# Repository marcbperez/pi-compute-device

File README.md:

# pi-compute-device

A portable device built with the Raspberry Pi Compute module.

## Installation

The schematics project is done in KiCad, free and available to most common
platforms. More information on how to download and install KiCad can be found in
its [official download page][download-kicad].

## Usage

Clone the sources and browse the package folder. The KiCad project is located in
`kicad-project/pi-compute-device.pro`.

```bash
git clone https://github.com/marcbperez/pi-compute-device
cd pi-compute-device
```

## Testing

There is no testing in place for this project yet.

## Troubleshooting

The [issue tracker][issue-tracker] intends to manage and compile bugs,
enhancements, proposals and tasks. Reading through its material or reporting to
its contributors via the platform is strongly recommended.

## Contributing

This project adheres to [Semantic Versioning][semver] and to certain syntax
conventions defined in [.editorconfig][editorconfig]. To get a list of changes
refer to the [CHANGELOG][changelog]. Only branches prefixed by *feature-*,
*hotfix-*, or *release-* will be considered:

  - Fork the project.
  - Create your new branch: `git checkout -b feature-my-feature develop`
  - Commit your changes: `git commit -am 'Added my new feature.'`
  - Push the branch: `git push origin feature-my-feature`
  - Submit a pull request.

## Credits

This project is created by [marcbperez][author] and maintained by its
[author][author] and contributors.

## License

This project is licensed under the [Apache License Version 2.0][license].

[author]: https://marcbperez.github.io
[issue-tracker]: https://github.com/marcbperez/pi-compute-device/issues
[editorconfig]: .editorconfig
[changelog]: CHANGELOG.md
[license]: LICENSE
[semver]: http://semver.org
[download-kicad]: http://kicad-pcb.org/download/

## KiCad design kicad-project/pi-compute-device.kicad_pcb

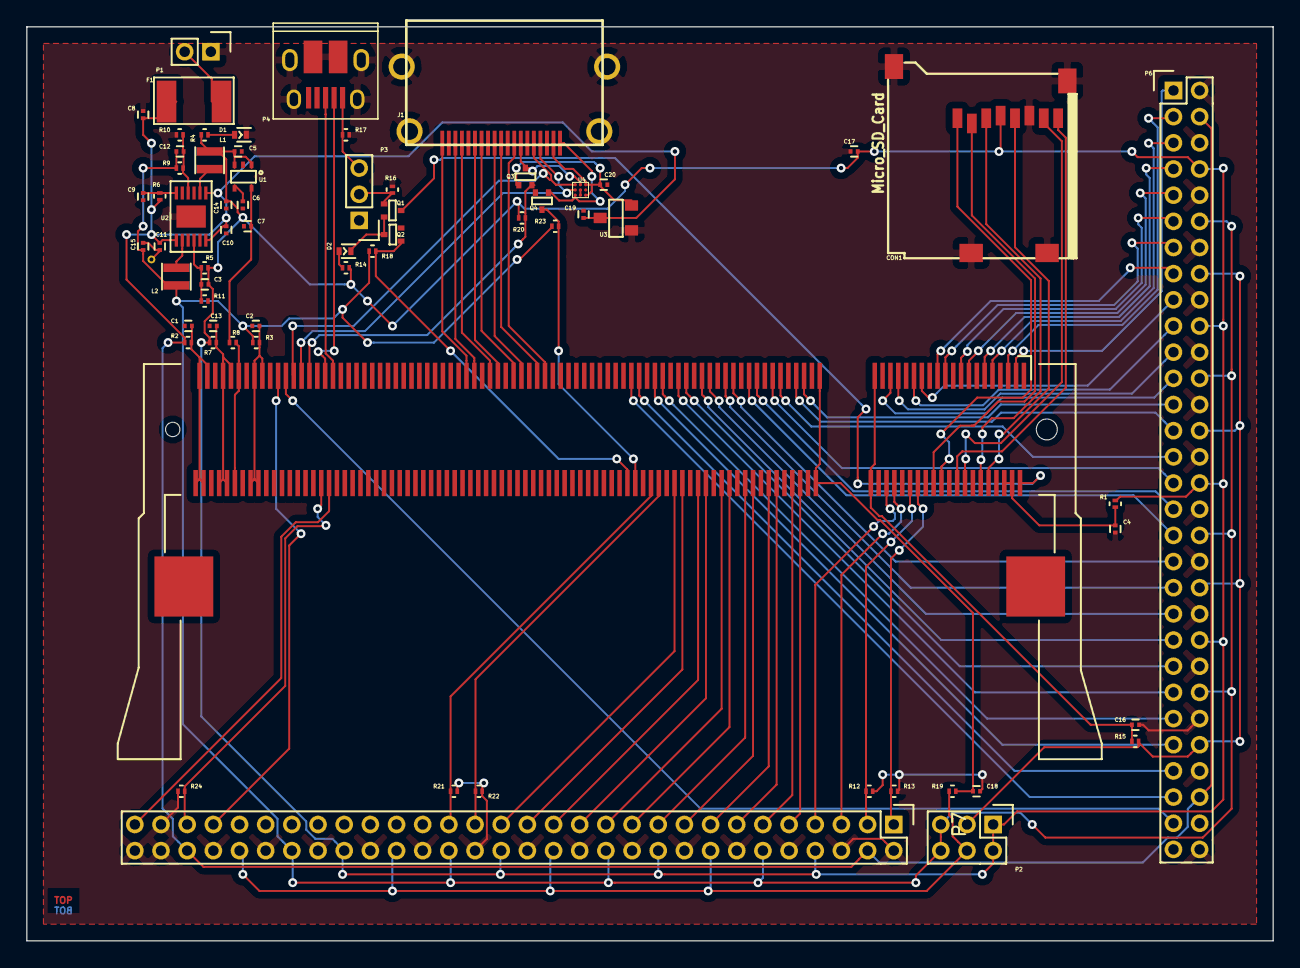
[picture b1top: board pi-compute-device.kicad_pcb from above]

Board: 2 copper layers, 95.2 x 69.8 mm, 66 parts (0 on the bottom side), 101 nets.

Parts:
C1, C2, C8, C13: 47u; C_0201
C3, C12: NF; C_0201
C4, C7, C17: 4.7u; C_0201
C5, C16, C18: 1u; C_0201
C6, C9, C19, C20: 100n; C_0201
C10, C11, C14, C15: 10u; C_0201
CON1: Micro_SD_Card; 2908-05WB-MG
D1, D2: LED; LED_0402
F1: MF-MSMF200
J1: 47151-1051; 10029449-111RLF
L1, L2: 4.7u; Inductor_Taiyo-Yuden_MD-2020
P1: CONN_01X02; Pin_Header_Straight_1x02_Pitch2.00mm
P2: CONN_02X03; Pin_Header_Straight_2x03_Pitch2.00mm
P3: CONN_01X03; Pin_Header_Straight_1x03_Pitch2.00mm
P4: USB_OTG; 10103594-0001LF
P5: DDR2_SODIMM_CM3; 1473005
P6, P7: CONN_02X30; Pin_Header_Straight_2x30_Pitch2.00mm
Q1, Q2, Q3, Q4: DMG1012T
R1, R2, R3, R5, R7, R8, R9, R15, R19: 0R; R_0201
R4, R14: 470R; R_0201
R6, R12, R13, R18, R21, R22, R23: 100K; R_0201
R10, R11, R20: NF; R_0201
R16, R17: 47K; R_0201
R24: 1K; R_0201
U1: AP7115-25SEG
U2: PAM2306AYPKE
U3: AP2331W
U4: ESD5384

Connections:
+1V8: C12.1, C15.1, L2.2, P2.5, P2.6, P6.12, P6.24, P6.36, P6.48, P7.12, P7.24, P7.36, P7.48, R3.2, R9.1, R18.1, R23.1
+2V5: C7.1, R8.2, U1.5
+3V3: C3.1, C5.1, C14.1, C17.1, CON1.4, L1.2, P2.1, P2.2, P6.8, P6.20, P6.32, P6.44, P7.8, P7.20, P7.32, P7.44, R1.1, R4.1, R5.1, R7.2, R14.1, R20.1, U1.1, U1.3
+5V: C8.1, C10.1, C11.1, C19.1, F1.1, P6.4, P6.56, P7.4, P7.56, R2.2, R6.1, U2.1, U2.6, U2.7, U3.3
/CEC: J1.13, Q3.D, U4.A2
/CM_1V8: C2.1, P5.183, P5.184, P5.185, P5.186, R3.1
/CM_3V3: C13.1, P5.191, P5.192, P5.193, P5.194, R7.1
/CM_VBAT: C1.1, P5.197, P5.198, P5.199, P5.200, R2.1
/CM_VDAC: P5.189, P5.190, R8.1
/EMMC_DISABLE_N: P5.2, Q1.D
/EMMC_EN_N_1V8: P5.90, Q2.G, R18.2
/GPIO0: P5.3, P6.1
/GPIO0-27_VREF: C16.1, P5.39, P5.40, R15.2
/GPIO1: P5.5, P6.3
/GPIO2: P5.9, P6.5
/GPIO3: P5.11, P6.7
/GPIO4: P5.15, P6.9
/GPIO5: P5.17, P6.11
/GPIO6: P5.21, P6.13
/GPIO7: P5.23, P6.15
/GPIO8: P5.27, P6.17
/GPIO9: P5.29, P6.19
/GPIO10: P5.33, P6.21
/GPIO11: P5.35, P6.23
/GPIO12: P5.45, P6.25
/GPIO13: P5.47, P6.27
/GPIO14: P5.51, P6.29
/GPIO15: P5.53, P6.31
/GPIO16: P5.57, P6.33
/GPIO17: P5.59, P6.35
/GPIO18: P5.63, P6.37
/GPIO19: P5.65, P6.39
/GPIO20: P5.69, P6.41
/GPIO21: P5.71, P6.43
/GPIO22: P5.75, P6.45
/GPIO23: P5.77, P6.47
/GPIO24: P5.81, P6.49
/GPIO25: P5.83, P6.51
/GPIO26: P5.87, P6.53
/GPIO27: P5.89, P6.55
/GPIO28: P5.28, P7.1, R13.1
/GPIO28-45_VREF: C18.1, P5.41, P5.42, R19.2
/GPIO29: P5.30, P7.3, R12.1
/GPIO30: P5.34, P7.5
/GPIO31: P5.36, P7.7
/GPIO32: P5.46, P7.9
/GPIO33: P5.48, P7.11
/GPIO34: P5.52, P7.13
/GPIO35: P5.54, P7.15
/GPIO36: P5.58, P7.17
/GPIO37: P5.60, P7.19
/GPIO38: P5.64, P7.21
/GPIO39: P5.66, P7.23
/GPIO40: P5.70, P7.25
/GPIO41: P5.72, P7.27
/GPIO42: P5.76, P7.29
/GPIO43: P5.78, P7.31
/GPIO44: P5.82, P7.33, R22.1
/GPIO45: P5.84, P7.35, R21.1
/H5V: C20.1, J1.18, Q3.G, U3.2, U4.A1, U4.C1
/HDMI_CEC: P5.171, Q3.S, R20.2
/HDMI_CK_N: J1.12, P5.111
/HDMI_CK_P: J1.10, P5.113
/HDMI_D0_N: J1.9, P5.117
/HDMI_D0_P: J1.7, P5.119
/HDMI_D1_N: J1.6, P5.123
/HDMI_D1_P: J1.4, P5.125
/HDMI_D2_N: J1.3, P5.129
/HDMI_D2_P: J1.1, P5.131
/HDMI_HPD: J1.19, Q4.G, U4.C3
/HDMI_HPD_N_1V8: P5.88, Q4.D, R23.2
/HDMI_SCL: J1.15, P5.175, U4.A3
/HDMI_SDA: J1.16, P5.173, U4.B3
/RUN: P5.177, P6.57
/SDX_CLK: CON1.5, P5.10
/SDX_CMD: CON1.3, P5.12
/SDX_D0: CON1.7, P5.16
/SDX_D1: CON1.8, P5.18
/SDX_D2: CON1.1, P5.22
/SDX_D3: CON1.2, P5.24
/SDX_VREF: C4.1, P5.4, P5.6, R1.2
/TVDAC: P5.166, P7.59
/USB_DM: P4.2, P5.167
/USB_DP: P4.3, P5.165
/USB_OTGID: P5.168, P7.55, R24.1
/VBUSB: P3.3, P4.1, R17.1
/VDD_CORE: P5.179, P7.53
/VG0: P2.3, P6.16, P6.28, P6.40, P6.52, R15.1
/VG1: P2.4, P7.16, P7.28, P7.40, P7.52, R19.1
GND: C1.2, C2.2, C4.2, C5.2, C6.2, C7.2, C8.2, C9.2, C10.2, C11.2, C13.2, C14.2, C15.2, C16.2, C17.2, C18.2, C19.2, C20.2, CON1.6, CON1.9, D1.1, J1.2, J1.5, J1.8, J1.11, J1.17, J1.SHIE, P1.1, P3.1, P4.5, P4.6, P5.1, P5.7, P5.8, P5.13, P5.14, P5.19, P5.20, P5.25, P5.26, P5.31, P5.32, P5.37, P5.38, P5.43, P5.44, P5.49, P5.50, P5.55, P5.56, P5.61, P5.62, P5.67, P5.68, P5.73, P5.74, P5.79, P5.80, P5.85, P5.86, P5.91, P5.92, P5.97, P5.98, P5.103, P5.104, P5.109, P5.110, P5.115, P5.116, P5.121, P5.122, P5.127, P5.133, P5.134, P5.139, P5.140, P5.145, P5.146, P5.151, P5.152, P5.157, P5.163, P5.164, P5.169, P5.170, P5.181, P5.182, P5.187, P5.188, P5.195, P5.196, P6.2, P6.6, P6.10, P6.14, P6.18, P6.22, P6.26, P6.30, P6.34, P6.38, P6.42, P6.46, P6.50, P6.54, P6.58, P6.60, P7.2, P7.6, P7.10, P7.14, P7.18, P7.22, P7.26, P7.30, P7.34, P7.38, P7.42, P7.46, P7.50, P7.54, P7.57, P7.58, P7.60, Q2.S, Q4.S, R10.1, R11.1, R12.2, R13.2, R16.2, R17.2, R21.2, R22.2, R24.2, U1.2, U2.3, U2.9, U2.13, U3.1, U4.B2, U4.C2
unnamed: C3.2, R5.2, R11.2, U2.4
unnamed: C6.1, U1.4
unnamed: C9.1, R6.2, U2.12
unnamed: C12.2, R9.2, R10.2, U2.10
unnamed: D1.2, R4.2
unnamed: D2.1, Q1.S, Q2.D
unnamed: D2.2, R14.2
unnamed: F1.2, P1.2
unnamed: L1.1, U2.8
unnamed: L2.1, U2.2
unnamed: P3.2, Q1.G, R16.1

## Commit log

2016-12-28 Added .gitignore list for untracked resources.
2016-12-29 Added a .gitignore list for untracked resources.
2016-12-29 Added an EditorConfig to suggest syntax and format standards.
2016-12-29 Bumped version to 0.1.0.
2016-12-29 Added a README which covers project description and usage.
2016-12-29 Added a LICENSE file to define project ownership and rights.
2016-12-29 Added this CHANGELOG file to document project changes and versions.
2016-12-30 Fixed small typographical errors on the README file.
2016-12-30 Added schematics project with DDR2 SODIMM connector for CM3.
2016-12-30 Included unreleased changes.
2016-12-30 Bumped version to 0.2.0.
2016-12-30 Added library for DDR2 SODIMM connector for CM3.
2016-12-31 Added power supply module to schematics.
2016-12-31 Bumped version to 0.3.0.
2016-12-31 Added library for AP7115-25SEG.
2016-12-31 Added library for PAM2306AYPKE.
2017-01-02 Added GPIO module to schematics.
2017-01-02 Bumped version to 0.4.0.
2017-01-03 Added library for DMG1012T.
2017-01-03 Added USB module to schematics.
2017-01-03 Bumped version to 0.5.0.
2017-01-04 Bumped version to 0.6.0.
2017-01-04 Added Micro SD Card module to schematics.
2017-01-05 Bumped version to 0.7.0.
2017-01-05 Added HDMI module to schematics.
2017-01-05 Added library for 47151-1051.
2017-01-05 Added library for ESD5384.
2017-01-05 Added library for AP2331W.
2017-01-06 Changed DMG1012T pin references on schematics.
2017-01-06 Changed DMG1012T pin names for main component.
2017-01-06 Bumped version to 0.8.0.
2017-01-06 Changed project information for DMG1012T.
2017-01-07 Bumped version to 0.9.0.
2017-01-07 Added MF-MSMF200 component datasheet.
2017-01-07 Added MF-MSMF200 component footprint and library.
2017-01-08 Added 1473005 component datasheet.
2017-01-08 Added 1473005 component footprint and library.
2017-01-08 Bumped version to 0.10.0.
2017-01-10 Added AP2331W component footprint and library.
2017-01-10 Bumped version to 0.11.0.
2017-01-10 Added AP2331W component datasheet.
2017-01-11 Bumped version to 0.12.0.
2017-01-11 Added AP7115-25SEG component footprint and library.
2017-01-11 Added AP7115-25SEG component datasheet.
2017-01-12 Added DMG1012T component datasheet.
2017-01-12 Bumped version to 0.13.0.
2017-01-12 Added DMG1012T component footprint and library.
2017-01-13 Bumped version to 0.14.0.
2017-01-13 Added ESD5384 component footprint and library.
2017-01-13 Added ESD5384 component datasheet.
2017-01-14 Added PAM2306AYPKE component footprint and library.
2017-01-14 Bumped version to 0.15.0.
2017-01-14 Added PAM2306AYPKE component datasheet.
2017-01-15 Added Schematics and board layout preview PDFs.
2017-01-15 Added 10103594-0001LF datasheet and footprint.
2017-01-15 Added project netlist.
2017-01-15 Changed PAM2306AYPKE and MF-MSMF200 components.
2017-01-15 Bumped version to 0.16.0.
2017-01-15 Added 2908-05WB-MG datasheet and footprint.
2017-01-15 Changed Git ignore list with new files.
2017-01-15 Added 10029449-111RLF datasheet and footprint.
2017-01-15 Added first partially routed board.
2017-01-15 Changed 10029449-111RLF as default HDMI connector.
2017-01-15 Added stitch footprint for layer stitching.
2017-01-15 Main project and schematics with new libraries and addons.
2017-01-29 Added project bill of materials.
2017-01-29 Bumped version to 0.17.0.
